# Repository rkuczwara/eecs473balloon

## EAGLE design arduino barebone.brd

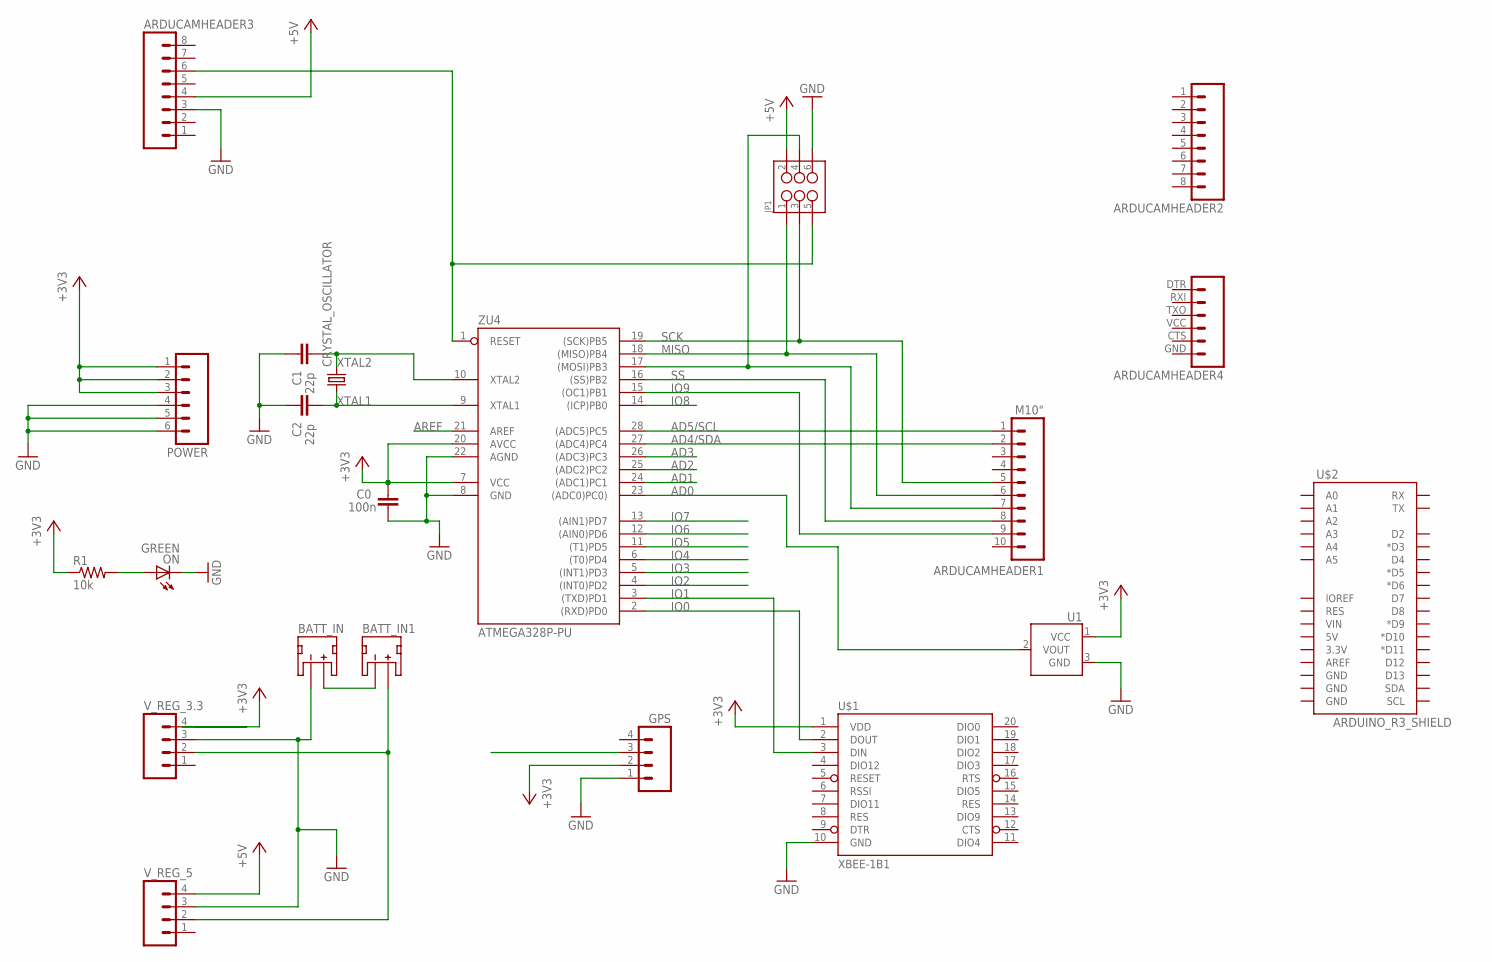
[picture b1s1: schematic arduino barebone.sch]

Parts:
ARDUCAMHEADER1: M10"; 1X10
ARDUCAMHEADER2, ARDUCAMHEADER3: M081X08; 1X08
ARDUCAMHEADER4: M06SIP; 1X06
BATT_IN, BATT_IN1: JST_2MM_MALE; JST-2-SMD
C0: 100n; C0603-ROUND
C1, C2: 22p; C0603-ROUND
CRYSTAL_OSCILLATOR: CRYSTALHC49US; HC49US
GPS: M04PTH; 1X04
JP1: M03X2POGO_PINS; 2X3_POGO
ON: GREEN; CHIP-LED0805
POWER: M06LONGPADS; 1X06_LONGPADS
R1: 10k; 0805
U1: TMP36GT9; TO-92
U$1: XBEE-1B1; XBEE-1
U$2: ARDUINO_R3_SHIELD; UNO_R3_SHIELD
V_REG_3.3, V_REG_5: M04PTH; 1X04
ZU4: ATMEGA328P-PU; DIL28-3

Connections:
+3V3: C0.2, GPS.2, POWER.1, POWER.2, POWER.3, R1.1, U1.1 (VCC), U$1.1 (VDD), V_REG_3.3.4, ZU4.7 (VCC), ZU4.20 (AVCC)
+5V: ARDUCAMHEADER3.4, JP1.P$2 (2), V_REG_5.4
AD0: U1.2 (VOUT), ZU4.23 ((ADC0)PC0))
AD1: ZU4.24 ((ADC1)PC1)
AD2: ZU4.25 ((ADC2)PC2)
AD3: ZU4.26 ((ADC3)PC3)
AD4/SDA: ARDUCAMHEADER1.2, ZU4.27 ((ADC4)PC4)
AD5/SCL: ARDUCAMHEADER1.1, ZU4.28 ((ADC5)PC5)
AREF: ZU4.21 (AREF)
GND: ARDUCAMHEADER3.3, BATT_IN.1 (-), C0.1, C1.2, C2.2, GPS.1, JP1.P$6 (6), ON.C, POWER.4, POWER.5, POWER.6, U1.3 (GND), U$1.10 (GND), V_REG_3.3.3, V_REG_5.3, ZU4.8 (GND), ZU4.22 (AGND)
IO0: U$1.2 (DOUT), ZU4.2 ((RXD)PD0)
IO1: U$1.3 (DIN), ZU4.3 ((TXD)PD1)
IO2: ZU4.4 ((INT0)PD2)
IO3: ZU4.5 ((INT1)PD3)
IO4: ZU4.6 ((T0)PD4)
IO5: ZU4.11 ((T1)PD5)
IO6: ZU4.12 ((AIN0)PD6)
IO7: ZU4.13 ((AIN1)PD7)
IO8: ZU4.14 ((ICP)PB0)
IO9: ARDUCAMHEADER1.9, ZU4.15 ((OC1)PB1)
MISO: ARDUCAMHEADER1.6, JP1.P$1 (1), ZU4.18 ((MISO)PB4)
unnamed: ON.A, R1.2
unnamed: BATT_IN.2 (+), BATT_IN1.1 (-)
unnamed: ARDUCAMHEADER1.7, JP1.P$4 (4), ZU4.17 ((MOSI)PB3)
unnamed: ARDUCAMHEADER3.6, JP1.P$5 (5), ZU4.1 (RESET)
SCK: ARDUCAMHEADER1.5, JP1.P$3 (3), ZU4.19 ((SCK)PB5)
SOFTWARE_SERIAL: GPS.3
SS: ARDUCAMHEADER1.8, ZU4.16 ((SS)PB2)
V_IN: BATT_IN1.2 (+), V_REG_3.3.2, V_REG_5.2
XTAL1: C2.1, CRYSTAL_OSCILLATOR.1, ZU4.9 (XTAL1)
XTAL2: C1.1, CRYSTAL_OSCILLATOR.2, ZU4.10 (XTAL2)

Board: 2 copper layers, 21 parts (0 on the bottom side), 19 nets, no tracks yet.

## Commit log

2014-10-27 adding Eagle files
2014-10-27 started placing components. arduino shield layout

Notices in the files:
parts and their libraries:
SparkFun-FreqCtrl: Licensing: Creative Commons ShareAlike 4.0 International - https://creativecommons.org/licenses/by-sa/4.0
